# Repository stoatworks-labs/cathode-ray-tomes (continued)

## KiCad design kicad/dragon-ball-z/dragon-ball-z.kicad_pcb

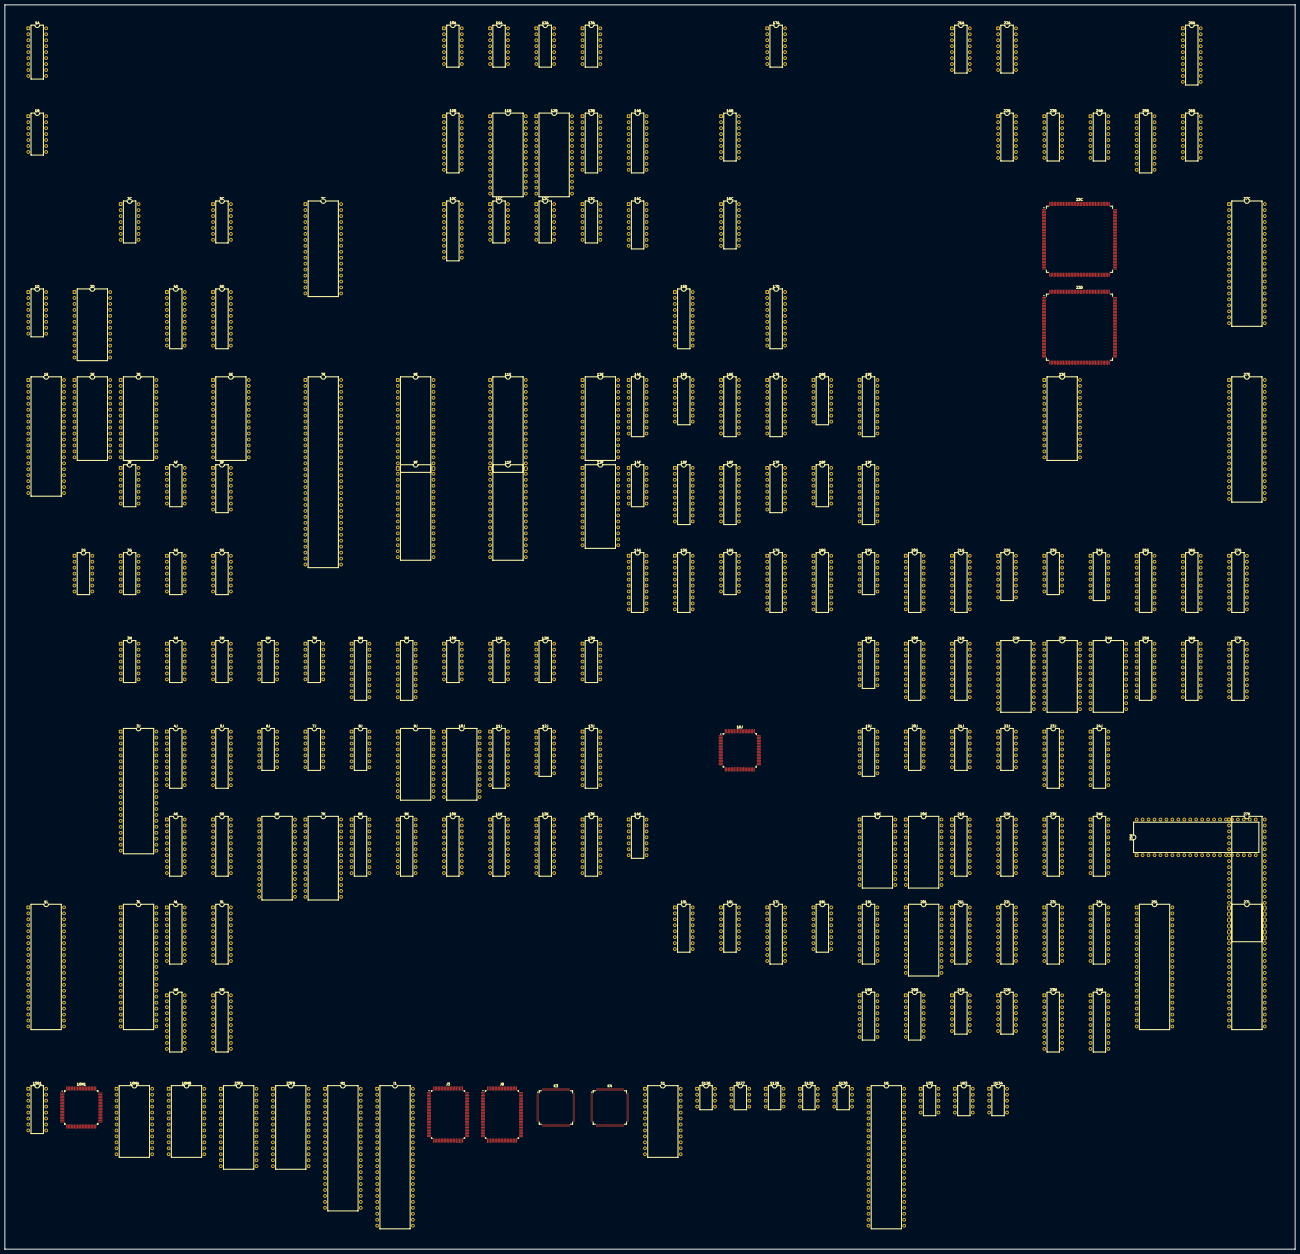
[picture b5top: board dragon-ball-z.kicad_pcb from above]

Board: 2 copper layers, 550.4 x 530.8 mm, 188 parts (0 on the bottom side), 1050 nets, no tracks yet.

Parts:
1A: DIP-18_W7.62mm
1B, 5C: DIP-14_W7.62mm
1D: YM3012; DIP-16_W7.62mm
1E: Z80; DIP-40_W15.24mm
1L, 3J, 3L, 25K, 25L, 27C, 27E, 27K, 27L: 065A08; DIP-42_W15.24mm
2D: YM2151; DIP-24_W15.24mm
2E, 3E, 23E, 23FA, 23FB: MB8464A-10W-15W; DIP-28_W15.24mm
2G: 74LS21; DIP-14_W7.62mm
3C: 4066; DIP-14_W7.62mm
3F, 4H, 5H, 7H, 7J, 11C, 14K, 17A: 74LS74; DIP-14_W7.62mm
3G, 3H, 13C, 14F, 16G, 18F, 22J: 74LS04; DIP-14_W7.62mm
4D, 8H, 9H: PAL16L8; DIP-20_W7.62mm
4F, 5G, 6J, 10H, 11H, 12C, 12H, 13H, 19G, 23G: 74LS32; DIP-14_W7.62mm
4G: 74LS10; DIP-14_W7.62mm
4J, 4K, 4L, 4M, 5D, 5J, 5K, 5L, 5M, 16F, 17E, 19E, 23L, 24J, 24K, 24L, 24M, 26H, 27H: 74LS374; DIP-20_W7.62mm
5E: 27256; DIP-28_W15.24mm
5F: 74LS148; DIP-16_W7.62mm
6H, 8J: 74LS08; DIP-14_W7.62mm
6K, 7K: MB8464A-80-10-15/L-LL; DIP-28_W15.24mm
7C: MS2M; DIP-32_W15.24mm
7E: 68000D; DIP-64_W15.24mm
8K, 9K, 10B, 10K, 11J, 11K, 12K, 13J, 13K, 14E, 14G, 25B, 26A: 74LS245; DIP-20_W7.62mm
9E, 9F, 11E, 11F: DIP-32_W15.24mm
9J, 10J, 16MA, 16MB: TMM2018_25_35_45; DIP-24_W15.24mm
10A, 11A, 12A, 13A: 74LS07; DIP-14_W7.62mm
10C, 13B, 14B, 15D, 17D, 17G, 17L: 74LS273; DIP-20_W7.62mm
11B, 12B, 13E, 13F: SRAM32K8B; DIP-28_W15.24mm
12J, 15L, 16L, 18L, 23B: 74LS367; DIP-16_W7.62mm
14C, 15B1, 16C, 17F, 18E, 19H, 19J, 19M, 20M, 22B, 22G, 24G: 74LS157; DIP-16_W7.62mm
15E, 16B: 74LS138; DIP-16_W7.62mm
15F, 19F, 20G, 20H, 21G, 21H, 21K, 22L, 23J, 23K, 23M, 27G: 74LS244; DIP-20_W7.62mm
15G, 19L, 21L, 22K, 25G, 25H: 74LS373; DIP-20_W7.62mm
16E: 74F245; DIP-20_W7.62mm
16H1, 16J: 053936; PQFP-80_14x14mm_P0.65mm
18G: PALACE16V8H-25; DIP-20_W7.62mm
19K, 20K, 20L, 22H, 23H, 24H: HM6116P-3; DIP-24_W15.24mm
20J, 21J, 21M, 22M: 74LS86; DIP-14_W7.62mm
21A, 22A, 24B, 26B: 74LS257; DIP-16_W7.62mm
23C: 054157; PQFP-160_28x28mm_P0.65mm
23D: 054156; PQFP-160_28x28mm_P0.65mm
26G: 74F374; DIP-20_W7.62mm
H1: 065A08; DIP-42_W15.24mm
I1: DIP-48_W15.24mm
J3, J8: 053251; PQFP-100_14x20mm_P0.65mm
K3: 053247; TQFP-120_14x14mm_P0.4mm
K4: 053246; TQFP-120_14x14mm_P0.4mm
S1: 051550; DIP-24_W15.24mm
S126, S127, S128, S129, S130: 005273; DIP-8_W7.62mm
U6: OKI6295; DIP-48_W15.24mm
U33, U63, U134: 052535; DIP-10_W7.62mm

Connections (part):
/3H10: 3F.11, 3H.10, 17G.11
/4D19: 4D.19, 11C.13
/4F6: 4F.6, 6H.13
/4HP5: 4H.5, 18G.7
/8H13: 8H.13, 9E.24, 9F.24, 11E.24, 11F.24, 18G.13
/8H19: 8H.19, 18G.5
/8JP11: 6H.4, 6J.4, 8J.11
/10C9: 10C.9, 14C.3
/10C12: 3F.4, 10C.12
/10h2: 3G.1, 3H.9, 3H.11, 3H.12, 7J.11, 10H.2, 19G.9, 19G.12, 23G.1
/12C2: 12C.2, 14C.12
/12C5: 12C.5, 14C.9
/13C8: 13C.3, 13C.8, 13C.11, 13C.13
/15E9: 15E.9, 18G.9, 23L.11, 26H.11
/16B11: 5D.11, 16B.11
/16B12: 10C.11, 16B.12
/16B14: 16B.14, 26A.19
/16B15: 18G.15, 23B.12, 25B.19
/16HCLK: 13C.4, 15D.11, 15G.11, 16F.11, 16H1.64, 17F.1, 19E.11, 19H.1, 22G.1, 24G.1, 24J.11, 25G.11, 25H.11, 26G.11, 27H.11
/16JCLK: 13C.10, 16J.64, 17D.11, 17E.11, 19J.1, 19L.11, 19M.1, 20M.1, 21L.11, 22K.11, 24K.11, 24L.11, 24M.11
/AS: 3H.2, 4H.4, 4H.10, 5H.4, 5H.10, 17G.1
/BCOL0: 17D.2, J3.4, J8.4, J8.51
/BCOL1: 17D.5, J3.5, J8.5, J8.52
/BCOL2: 17D.6, J3.6, J8.6, J8.54
/BCOL3: 17D.9, J3.7, J8.7, J8.55
/BCOL4: 17D.12, J3.55, J8.8
/BCOL5: 17D.15, J3.56, J8.9
/BDB0: 15F.18, 15G.3, 16F.3, 22H.9
/BDB1: 15F.16, 15G.4, 16F.4, 22H.10
/BDB2: 15F.14, 15G.7, 16F.7, 22H.11
/BDB3: 15F.12, 15G.8, 16F.8, 22H.13
/BDB4: 15F.9, 15G.13, 16F.13, 22H.14
/BDB5: 15F.7, 15G.14, 16F.14, 22H.15
/BDB6: 15F.5, 15G.17, 16F.17, 20J.2, 21J.2, 21J.5, 21J.13, 22H.16
/BDB7: 15F.3, 15G.18, 20J.5, 20J.10, 20J.13, 21J.9, 22H.17
/BDB8: 20H.18, 23H.9, 25H.3, 27H.3
/BDB9: 20H.16, 23H.10, 25H.4, 27H.4
/BDB10: 20H.14, 23H.11, 25H.7, 27H.7
/BDB11: 20H.12, 23H.13, 25H.8, 27H.8
/BDB12: 20H.9, 23H.14, 25H.13, 27H.13
/BDB13: 20H.7, 23H.15, 25H.14, 27H.14
/BDB14: 20H.5, 23H.16, 25H.17, 27H.17
/BDB15: 20H.3, 23H.17, 25H.18, 27H.18
/BDB16: 21H.18, 24H.9, 25G.3, 26G.3
/BDB17: 21H.16, 24H.10, 25G.4, 26G.4
/BDB18: 21H.14, 24H.11, 25G.7, 26G.7
/BDB19: 21H.12, 24H.13, 25G.8, 26G.8
/BDB20: 21H.9, 24H.14, 25G.13, 26G.13
/BDB21: 21H.7, 24H.15, 25G.14, 26G.14
/BDB22: 21H.5, 24H.16, 25G.17, 26G.17
/BDB23: 21H.3, 24H.17, 25G.18, 26G.18
/BNK~SCR: 15E.13, 23C.64
/CI0: 23C.154, J3.57, J8.57
/CI1: 23C.153, J3.58, J8.58
/CI2: 23C.51, J3.59, J8.59
/CI3: 23C.52, J3.60, J8.60
/CI4: 23C.143, J8.61
/CI5: 23C.142, J8.62
/CI6: 23C.141, J8.63
/CI7: 23C.138, J8.64
/CLK1: 3H.13, I1.8
/CLK2: 22J.5, I1.9
/CLKMIX: 3G.3, 7H.12, 11C.3, 13B.11, 13C.12, 14B.11, 14K.11, 17A.3, 17A.11, J3.41, J8.41
/COA7: 16C.3, J3.11
/COA8: 16C.6, J3.93
/COA9: 16C.10, J3.92
/COA10: 16C.13, J3.91
/COB0: 15B1.3, J8.19
/COB1: 15B1.6, J8.18
/COB2: 15B1.10, J8.17
/COB3: 15B1.13, J8.16
/COB4: 22B.3, J8.14
/COB5: 22B.6, J8.13
/COB6: 22B.10, J8.12
/COB7: 22B.13, J8.11
/COIN_CNT_1: S1.22, S1.23
/COIN_CNT_2: S1.20, S1.21
/CPG~CS: 16B.7, J3.81, J8.81
/CR~CS: 15E.15, K3.9
/CTRB: 3C.5, 5D.1, 10C.16, 14F.13
/DAO: 5C.3, U6.36
/FCOL0: 23C.152, J3.66, J8.66
/FCOL1: 23C.151, J3.67, J8.67
/FCOL2: 23C.53, J3.68, J8.68
/FCOL3: 23C.54, J3.69, J8.69
/FPAL0: 23C.135, J8.70
/FPAL1: 23C.134, J8.71
/FPAL2: 23C.133, J8.72
/FPAL3: 23C.132, J8.73
/GFXROMA0: 23D.159, 27C.10, 27E.10
/GFXROMA1: 23D.158, 27C.9, 27E.9
/GFXROMA2: 23D.157, 27C.8, 27E.8
/GFXROMA3: 23D.156, 27C.7, 27E.7
/GFXROMA4: 23D.155, 27C.6, 27E.6
/GFXROMA5: 23D.154, 27C.5, 27E.5
/GFXROMA6: 23D.153, 27C.4, 27E.4
/GFXROMA7: 23D.152, 27C.3, 27E.3
/GFXROMA8: 23D.151, 27C.41, 27E.41
/GFXROMA9: 23D.149, 27C.40, 27E.40
/GFXROMA10: 23D.148, 27C.39, 27E.39
/GFXROMA11: 23D.147, 27C.38, 27E.38
/GFXROMA12: 23D.146, 27C.37, 27E.37
/GFXROMA13: 23D.145, 27C.36, 27E.36
/GFXROMA14: 23D.144, 27C.35, 27E.35
/GFXROMA15: 23D.143, 27C.34, 27E.34
/GFXROMA16: 23D.142, 27C.33, 27E.33
/GFXROMA17: 23D.141, 27C.2, 27E.2
/GFXROMA18: 23D.138, 27C.1, 27E.1
/GFXROMD0: 23C.16, 27C.14
/GFXROMD1: 23C.17, 27C.16
/GFXROMD2: 23C.18, 27C.18
/GFXROMD3: 23C.19, 27C.20
/GFXROMD4: 23C.9, 27C.23
/GFXROMD5: 23C.11, 27C.25
/GFXROMD6: 23C.12, 27C.27
/GFXROMD7: 23C.13, 27C.29
/GFXROMD8: 23C.3, 27C.15
/GFXROMD9: 23C.4, 27C.17
/GFXROMD10: 23C.5, 27C.19
/GFXROMD11: 23C.6, 27C.21
/GFXROMD12: 23C.155, 27C.24
/GFXROMD13: 23C.156, 27C.26
/GFXROMD14: 23C.157, 27C.28
/GFXROMD15: 23C.158, 27C.30
/GFXROMD16: 23C.44, 27E.14
/GFXROMD17: 23C.45, 27E.16
/GFXROMD18: 23C.46, 27E.18
/GFXROMD19: 23C.47, 27E.20
/GFXROMD20: 23C.36, 27E.23
/GFXROMD21: 23C.37, 27E.25
/GFXROMD22: 23C.38, 27E.27
/GFXROMD23: 23C.39, 27E.29
/GFXROMD24: 23C.29, 27E.15
/GFXROMD25: 23C.31, 27E.17
/GFXROMD26: 23C.32, 27E.19
/GFXROMD27: 23C.33, 27E.21
/GFXROMD28: 23C.23, 27E.24
/GFXROMD29: 23C.24, 27E.26
/GFXROMD30: 23C.25, 27E.28
/GFXROMD31: 23C.26, 27E.30
/IO/1P_BTN_1_D: 22A.11, S126.3
/IO/1P_BTN_2_D: 22A.5, S128.7
/IO/1P_BTN_3_D: 22A.2, S128.3
/IO/1P_DOWN_D: 21A.14, S130.5
/IO/1P_LEFT_D: 24B.11, S130.3
/IO/1P_RIGHT_D: 24B.5, S126.7
/IO/1P_START_D: 22A.6, S127.7
/IO/1P_UP_D: 24B.2, S127.3
/IO/2P_BTN_1_D: 21A.11, S126.1
/IO/2P_BTN_2_D: 21A.5, S128.5
/IO/2P_BTN_3_D: 21A.2, S128.1
/IO/2P_DOWN_D: 22A.14, S130.7
/IO/2P_LEFT_D: 26B.11, S130.1
/IO/2P_RIGHT_D: 26B.5, S126.5
/IO/2P_START_D: 22A.3, S127.5
/IO/2P_UP_D: 26B.2, S127.1
/IO/COIN_1_D: 24B.6, S129.3
/IO/COIN_2_D: 24B.3, S129.1
/IO/SERVICE1_D: 22A.10, S129.7
/IO/TEST_D: 22A.13, S129.5
/IO/VSS: 21A.3, 21A.6, 23B.1, 23B.15, 24B.10, 24B.13, 24B.14, 26B.14
/IOE: 16B.15, 21A.15, 22A.15, 24B.15, 26B.15
/IPL0: 5F.9, 7E.25
/IPL1: 5F.7, 7E.24
/IPL2: 5F.6, 7E.23
/M16B: 3G.2, 14F.3, 23B.2, 23C.111, 23D.122
/MAIN_A1: 7E.29, 9E.12, 9F.12, 11E.12, 11F.12, 12J.2, 13E.10, 13F.10, 14G.2, 16L.2, J3.85, J8.85
/MAIN_A2: 7E.30, 9E.11, 9F.11, 11E.11, 11F.11, 12J.4, 13E.9, 13F.9, 14G.3, 16L.4, J3.84, J8.84
/MAIN_A3: 7E.31, 9E.10, 9F.10, 11E.10, 11F.10, 12J.6, 13E.8, 13F.8, 14G.4, 16L.6, J3.83, J8.83
/MAIN_A4: 7E.32, 9E.9, 9F.9, 11E.9, 11F.9, 12J.10, 13E.7, 13F.7, 14G.5, 16L.10, J3.82, J8.82
/MAIN_A5: 7E.33, 9E.8, 9F.8, 11E.8, 11F.8, 12J.12, 13E.6, 13F.6, 14G.6, 16L.12
/MAIN_A6: 7E.34, 9E.7, 9F.7, 11E.7, 11F.7, 12J.14, 13E.5, 13F.5, 14G.7, 16L.14
/MAIN_A7: 7E.35, 9E.6, 9F.6, 11E.6, 11F.6, 13E.4, 13F.4, 14G.8, 15L.2, 18L.2
/MAIN_A8: 7E.36, 9E.5, 9F.5, 11E.5, 11F.5, 13E.3, 13F.3, 14G.9, 15L.4, 18L.4
/MAIN_A9: 7E.37, 9E.27, 9F.27, 11E.27, 11F.27, 13E.25, 13F.25, 15L.6, 16E.2, 18L.6
/MAIN_A10: 7E.38, 9E.26, 9F.26, 11E.26, 11F.26, 13E.24, 13F.24, 15L.10, 16E.3, 18L.10
/MAIN_A11: 7E.39, 9E.23, 9F.23, 11E.23, 11F.23, 13E.21, 13F.21, 15L.12, 16E.4, 18L.12
/MAIN_A12: 7E.40, 9E.25, 9F.25, 11E.25, 11F.25, 13E.23, 13F.23, 15L.14, 16E.5, 18L.14
/MAIN_A13: 7E.41, 9E.4, 9F.4, 11E.4, 11F.4, 13E.2, 13F.2, 16E.6
/MAIN_A14: 7E.42, 9E.28, 9F.28, 11E.28, 11F.28, 13E.26, 13F.26, 16E.7
/MAIN_A15: 7E.43, 8H.11, 9E.29, 9F.29, 9H.11, 11E.29, 11F.29, 13E.1, 13F.1, 16E.8
/MAIN_A16: 7E.44, 8H.9, 9E.3, 9F.3, 9H.9, 11E.3, 11F.3, 16E.9
/MAIN_A17: 7E.45, 8H.8, 9E.2, 9F.2, 9H.8, 11E.2, 11F.2, 13C.5, 16B.6
/MAIN_A18: 7E.46, 8H.7, 9E.30, 9F.30, 9H.7, 11E.30, 11F.30
/MAIN_A19: 7E.47, 8H.6, 9E.31, 9F.31, 9H.6, 11E.31, 11F.31
/MAIN_A20: 7E.48, 8H.5, 9H.5
/MAIN_A21: 7E.50, 8H.4, 9H.4
/MAIN_A22: 7E.51, 8H.3, 9H.3
/MAIN_A23: 7E.52, 8H.2, 9H.2
/MAIN_AB0: 3H.3, 5G.1, 11K.2, 12H.1, 14G.18, 15B1.2, 16H1.74, 16J.74, 23B.10, 23C.74, 23D.95, 23J.2, 23M.2, 24G.6, I1.42, K3.7, K4.7
/MAIN_AB1: 11K.3, 14G.17, 15B1.5, 16H1.72, 16J.72, 21A.1, 22A.1, 23B.6, 23C.75, 23D.96, 23J.4, 24B.1, 26B.1, I1.41, K3.6, K4.6
/MAIN_AB2: 11K.4, 14G.16, 15B1.11, 16H1.71, 16J.71, 23D.97, 23J.6, 23M.4, I1.40
/MAIN_AB3: 11K.5, 14G.15, 15B1.14, 16H1.70, 16J.70, 23D.98, 23J.8, 23M.6, I1.38
/MAIN_AB4: 11K.6, 14G.14, 22B.2, 23D.99, 23J.11, 23M.8
/MAIN_AB5: 11K.7, 14G.13, 22B.5, 23D.101, 23J.13, 23M.11
/MAIN_AB6: 11K.8, 14G.12, 22B.11, 23D.102, 23J.15, 23M.13
/MAIN_AB7: 11K.9, 14G.11, 22B.14, 23D.103, 23J.17, 23M.15
/MAIN_AB8: 8K.2, 16C.2, 16E.18, 23D.104, 23K.2, 23M.17, 27G.2
/MAIN_AB9: 8K.3, 16C.5, 16E.17, 23D.105, 23K.4, 27G.4
/MAIN_AB10: 8K.4, 16C.11, 16E.16, 23D.106, 23K.6, 27G.6
/MAIN_AB11: 8K.5, 16C.14, 16E.15, 23D.107, 23K.8, 27G.8
/MAIN_AB12: 8K.6, 16E.14, 18G.19, 23D.108, 23K.11, 27G.11
/MAIN_AB13: 14C.2, 15E.1, 16B.1, 16E.13, 23K.13, 27G.13
/MAIN_AB14: 15E.2, 16B.2, 16E.12, 23K.15, 27G.15
/MAIN_AB15: 15E.3, 16B.3, 16E.11, 23K.17, 27G.17
/MAIN_D0: 5D.3, 7E.5, 9F.13, 9K.2, 10B.2, 10C.3, 13F.11, 18G.12, 22A.4, 23C.76, 23D.76, 25B.2, 26A.18, I1.13, J3.80, J8.80, K3.30
/MAIN_D1: 5D.4, 7E.4, 9F.14, 9K.3, 10B.3, 10C.4, 13F.12, 22A.7, 23C.77, 23D.77, 25B.3, 26A.17, I1.14, J3.79, J8.79, K3.29
/MAIN_D2: 5D.7, 7E.3, 9F.15, 9K.4, 10B.4, 10C.7, 13F.13, 22A.12, 23C.78, 23D.78, 25B.4, 26A.16, I1.15, J3.77, J8.77, K3.28
/MAIN_D3: 5D.8, 7E.2, 9F.17, 9K.5, 10B.5, 10C.8, 13F.15, 22A.9, 23C.79, 23D.79, 25B.5, 26A.15, I1.16, J3.76, J8.76, K3.27
/MAIN_D4: 5D.13, 7E.1, 9F.18, 9K.6, 10B.6, 10C.13, 13F.16, 23C.82, 23D.82, 24B.4, 25B.6, 26A.14, I1.18, J3.75, J8.75, K3.26
/MAIN_D5: 5D.14, 7E.64, 9F.19, 9K.7, 10B.7, 10C.14, 13F.17, 23C.83, 23D.83, 24B.7, 25B.7, 26A.13, I1.19, J3.74, J8.74, K3.25
/MAIN_D6: 5D.17, 7E.63, 9F.20, 9K.8, 10B.8, 10C.17, 13F.18, 23C.84, 23D.84, 24B.12, 25B.8, 26A.12, I1.20, K3.24
/MAIN_D7: 5D.18, 7E.62, 9F.21, 9K.9, 10B.9, 10C.18, 13F.19, 23C.85, 23D.85, 24B.9, 25B.9, 26A.11, I1.21, K3.23
/MAIN_D8: 7E.61, 9E.13, 10K.2, 13E.11, 14E.2, 21A.4, 23C.86, 23D.86, K3.22
/MAIN_D9: 7E.60, 9E.14, 10K.3, 13E.12, 14E.3, 21A.7, 23C.87, 23D.87, K3.20
/MAIN_D10: 7E.59, 9E.15, 10K.4, 13E.13, 14E.4, 21A.9, 23C.88, 23D.88, K3.19
/MAIN_D11: 7E.58, 9E.17, 10K.5, 13E.15, 14E.5, 21A.12, 23C.89, 23D.89, K3.18
/MAIN_D12: 7E.57, 9E.18, 10K.6, 13E.16, 14E.6, 23C.91, 23D.91, 26B.4, K3.17
/MAIN_D13: 7E.56, 9E.19, 10K.7, 13E.17, 14E.7, 23C.92, 23D.92, 26B.7, K3.15
/MAIN_D14: 7E.55, 9E.20, 10K.8, 13E.18, 14E.8, 23C.93, 23D.93, 26B.12, K3.14
/MAIN_D15: 7E.54, 9E.21, 10K.9, 13E.19, 14E.9, 23C.94, 23D.94, 26B.9, K3.13
/MAIN_PSAC/MAIN_D0: 11J.2, 12K.2, 15F.2, 19F.18, 20G.18, 21G.2
/MAIN_PSAC/MAIN_D1: 11J.3, 12K.3, 15F.4, 19F.16, 20G.16, 21G.4
/MAIN_PSAC/MAIN_D2: 11J.4, 12K.4, 15F.6, 19F.14, 20G.14, 21G.6
/MAIN_PSAC/MAIN_D3: 11J.5, 12K.5, 15F.8, 19F.12, 20G.12, 21G.8
/MAIN_PSAC/MAIN_D4: 11J.6, 12K.6, 15F.11, 19F.9, 20G.9, 21G.11
/MAIN_PSAC/MAIN_D5: 11J.7, 12K.7, 15F.13, 19F.7, 20G.7, 21G.13
/MAIN_PSAC/MAIN_D6: 11J.8, 12K.8, 15F.15, 19F.5, 20G.5, 21G.15
/MAIN_PSAC/MAIN_D7: 11J.9, 12K.9, 15F.17, 19F.3, 20G.3, 21G.17
/MAIN_PSAC/MAIN_D8: 13J.2, 13K.2
/MAIN_PSAC/MAIN_D9: 13J.3, 13K.3
/MAIN_PSAC/MAIN_D10: 13J.4, 13K.4
/MAIN_PSAC/MAIN_D11: 13J.5, 13K.5
/MAIN_PSAC/MAIN_D12: 13J.6, 13K.6
/MAIN_PSAC/MAIN_D13: 13J.7, 13K.7
/MAIN_PSAC/MAIN_D14: 13J.8, 13K.8
/MAIN_PSAC/MAIN_D15: 13J.9, 13K.9
/MAIN_PSAC/MOROE0: 8J.13, 9H.19, 12H.4
/MAIN_PSAC/MOROE4: 5G.4, 9H.15, 23G.4, 23G.12
/MAIN_PSAC/MOROE7: 6H.1, 6J.1, 9H.12
/MAIN_PSAC/NDMA_A: 16G.5, 16J.47
/MAIN_PSAC/NDMA_B: 16G.9, 16H1.47
/MAIN_PSAC/POEB: 4F.3, 15F.1, 15F.19, 20H.1, 20H.19, 21H.1, 21H.19
/MAIN_PSAC/PSAC_1/LA0: 16J.53, 16L.7, 16MA.6, 16MB.6
/MAIN_PSAC/PSAC_1/LA1: 16J.54, 16L.9, 16MA.5, 16MB.5
/MAIN_PSAC/PSAC_1/LA2: 16J.55, 16L.11, 16MA.4, 16MB.4
/MAIN_PSAC/PSAC_1/LA3: 16J.56, 16L.13, 16MA.3, 16MB.3
/MAIN_PSAC/PSAC_1/LA4: 15L.3, 16J.57, 16MA.2, 16MB.2
/MAIN_PSAC/PSAC_1/LA5: 15L.5, 16J.58, 16MA.1, 16MB.1
/MAIN_PSAC/PSAC_1/LA6: 15L.7, 16J.59, 16MA.23, 16MB.23
/MAIN_PSAC/PSAC_1/LA7: 15L.9, 16J.60, 16MA.22, 16MB.22
/MAIN_PSAC/PSAC_1/LA8: 15L.11, 16J.61, 16MA.19, 16MB.19
/MAIN_PSAC/PSAC_1/LH1: 16J.50, 16L.3, 16MA.8, 16MB.8
/MAIN_PSAC/PSAC_1/LH2: 16J.51, 16L.5, 16MA.7, 16MB.7
/MAIN_PSAC/PSAC_1/LUTD0: 12K.18, 16J.29, 16MB.9
/MAIN_PSAC/PSAC_1/LUTD1: 12K.17, 16J.30, 16MB.10
/MAIN_PSAC/PSAC_1/LUTD2: 12K.16, 16J.31, 16MB.11
/MAIN_PSAC/PSAC_1/LUTD3: 12K.15, 16J.32, 16MB.13
/MAIN_PSAC/PSAC_1/LUTD4: 12K.14, 16J.34, 16MB.14
/MAIN_PSAC/PSAC_1/LUTD5: 12K.13, 16J.35, 16MB.15
/MAIN_PSAC/PSAC_1/LUTD6: 12K.12, 16J.36, 16MB.16
/MAIN_PSAC/PSAC_1/LUTD7: 12K.11, 16J.37, 16MB.17
/MAIN_PSAC/PSAC_1/LUTD8: 13K.18, 16J.38, 16MA.9
/MAIN_PSAC/PSAC_1/LUTD9: 13K.17, 16J.39, 16MA.10
/MAIN_PSAC/PSAC_1/LUTD10: 13K.16, 16J.40, 16MA.11
/MAIN_PSAC/PSAC_1/LUTD11: 13K.15, 16J.41, 16MA.13
/MAIN_PSAC/PSAC_1/LUTD12: 13K.14, 16J.43, 16MA.14
/MAIN_PSAC/PSAC_1/LUTD13: 13K.13, 16J.44, 16MA.15
/MAIN_PSAC/PSAC_1/LUTD14: 13K.12, 16J.45, 16MA.16
/MAIN_PSAC/PSAC_1/LUTD15: 13K.11, 16J.46, 16MA.17
/MAIN_PSAC/PSAC_1/ROM1/BD0: 19K.9, 19L.3, 22L.18, 24L.3
/MAIN_PSAC/PSAC_1/ROM1/BD1: 19K.10, 19L.4, 22L.16, 24L.4
/MAIN_PSAC/PSAC_1/ROM1/BD2: 19K.11, 19L.7, 22L.14, 24L.7
/MAIN_PSAC/PSAC_1/ROM1/BD3: 19K.13, 19L.8, 22L.12, 24L.8
/MAIN_PSAC/PSAC_1/ROM1/BD4: 19K.14, 19L.13, 22L.9, 24L.13
/MAIN_PSAC/PSAC_1/ROM1/BD5: 19K.15, 19L.14, 22L.7, 24L.14
/MAIN_PSAC/PSAC_1/ROM1/BD6: 19K.16, 19L.17, 21M.5, 21M.10, 22L.5, 22M.5, 22M.10, 24L.17
/MAIN_PSAC/PSAC_1/ROM1/BD7: 19K.17, 19L.18, 21M.2, 21M.13, 22L.3, 22M.2, 22M.13, 24L.18
/MAIN_PSAC/PSAC_1/ROM1/BD8: 20K.9, 21K.18, 22K.3, 24K.3
/MAIN_PSAC/PSAC_1/ROM1/BD9: 20K.10, 21K.16, 22K.4, 24K.4
/MAIN_PSAC/PSAC_1/ROM1/BD10: 20K.11, 21K.14, 22K.7, 24K.7
/MAIN_PSAC/PSAC_1/ROM1/BD11: 20K.13, 21K.12, 22K.8, 24K.8
/MAIN_PSAC/PSAC_1/ROM1/BD12: 20K.14, 21K.9, 22K.13, 24K.13
/MAIN_PSAC/PSAC_1/ROM1/BD13: 20K.15, 21K.7, 22K.14, 24K.14
/MAIN_PSAC/PSAC_1/ROM1/BD14: 20K.16, 21K.5, 22K.17, 24K.17
/MAIN_PSAC/PSAC_1/ROM1/BD15: 20K.17, 21K.3, 22K.18, 24K.18
/MAIN_PSAC/PSAC_1/ROM1/BD16: 20L.9, 21L.3
/MAIN_PSAC/PSAC_1/ROM1/BD17: 20L.10, 21L.4
/MAIN_PSAC/PSAC_1/ROM1/BD18: 20L.11, 21L.7
/MAIN_PSAC/PSAC_1/ROM1/BD19: 20L.13, 21L.8
/MAIN_PSAC/PSAC_1/ROM1/BD20: 20L.14, 21L.13
/MAIN_PSAC/PSAC_1/ROM1/BD21: 20L.15, 21L.14
/MAIN_PSAC/PSAC_1/ROM1/BD22: 20L.16, 21L.17
/MAIN_PSAC/PSAC_1/ROM1/BD23: 20L.17, 21L.18
/MAIN_PSAC/PSAC_1/ROM1/DK1: 23L.19, 24K.19
/MAIN_PSAC/PSAC_1/ROM1/MAIN_D0: 19L.2, 21L.2, 22L.2, 23L.3
/MAIN_PSAC/PSAC_1/ROM1/MAIN_D1: 19L.5, 21L.5, 22L.4, 23L.4
/MAIN_PSAC/PSAC_1/ROM1/MAIN_D2: 19L.6, 21L.6, 22L.6, 23L.7
/MAIN_PSAC/PSAC_1/ROM1/MAIN_D3: 19L.9, 21L.9, 22L.8, 23L.8
/MAIN_PSAC/PSAC_1/ROM1/MAIN_D4: 19L.12, 21L.12, 22L.11, 23L.13
/MAIN_PSAC/PSAC_1/ROM1/MAIN_D5: 19L.15, 21L.15, 22L.13, 23L.14
/MAIN_PSAC/PSAC_1/ROM1/MAIN_D6: 19L.16, 21L.16, 22L.15, 23L.17
/MAIN_PSAC/PSAC_1/ROM1/MAIN_D7: 19L.19, 21L.19, 22L.17, 23L.18
/MAIN_PSAC/PSAC_1/ROM1/MAIN_D8: 21K.2, 22K.2
/MAIN_PSAC/PSAC_1/ROM1/MAIN_D9: 21K.4, 22K.5
/MAIN_PSAC/PSAC_1/ROM1/MAIN_D10: 21K.6, 22K.6
/MAIN_PSAC/PSAC_1/ROM1/MAIN_D11: 21K.8, 22K.9
/MAIN_PSAC/PSAC_1/ROM1/MAIN_D12: 21K.11, 22K.12
/MAIN_PSAC/PSAC_1/ROM1/MAIN_D13: 21K.13, 22K.15
/MAIN_PSAC/PSAC_1/ROM1/MAIN_D14: 21K.15, 22K.16
/MAIN_PSAC/PSAC_1/ROM1/MAIN_D15: 21K.17, 22K.19
/MAIN_PSAC/PSAC_1/ROM1/PLOE: 23L.16, 24K.16, 25L.13
/MAIN_PSAC/PSAC_1/ROM1/RA_LOW: 23M.16, 24M.5, 25L.30
/MAIN_PSAC/PSAC_1/ROM1/VA0: 19K.8, 20K.8, 20L.8, 20M.7
/MAIN_PSAC/PSAC_1/ROM1/VA1: 19K.7, 20K.7, 20L.7, 20M.9
/MAIN_PSAC/PSAC_1/ROM1/VA2: 19K.6, 20K.6, 20L.6, 20M.12
/MAIN_PSAC/PSAC_1/ROM1/VA3: 19K.5, 19M.4, 20K.5, 20L.5
/MAIN_PSAC/PSAC_1/ROM1/VA4: 19K.4, 19M.7, 20K.4, 20L.4
/MAIN_PSAC/PSAC_1/ROM1/VA5: 19K.3, 19M.9, 20K.3, 20L.3
/MAIN_PSAC/PSAC_1/ROM1/VA6: 19K.2, 19M.12, 20K.2, 20L.2
/MAIN_PSAC/PSAC_1/ROM1/VA7: 19J.4, 19K.1, 20K.1, 20L.1
/MAIN_PSAC/PSAC_1/ROM1/VA8: 19J.7, 19K.23, 20K.23, 20L.23
/MAIN_PSAC/PSAC_1/ROM1/VA9: 19J.9, 19K.22, 20K.22, 20L.22
/MAIN_PSAC/PSAC_1/ROM1/VA10: 19J.12, 19K.19, 20K.19, 20L.19
/MAIN_PSAC/PSAC_1/VSS: 16J.2, 16J.12, 16J.23, 16J.28, 16J.42, 16J.52, 16J.63, 16J.75, 16MA.18, 16MB.18
/MAIN_PSAC/PSAC_1/X0: 16J.26, 21M.1
/MAIN_PSAC/PSAC_1/X1: 16J.25, 22M.1
/MAIN_PSAC/PSAC_1/X2: 16J.24, 21M.12
/MAIN_PSAC/PSAC_1/X3: 16J.22, 22M.12
/MAIN_PSAC/PSAC_1/X4: 16J.21, 20M.5
/MAIN_PSAC/PSAC_1/X5: 16J.20, 20M.11
/MAIN_PSAC/PSAC_1/X6: 16J.19, 20M.14
/MAIN_PSAC/PSAC_1/X7: 16J.18, 19M.2
/MAIN_PSAC/PSAC_1/X8: 16J.17, 19M.5
/MAIN_PSAC/PSAC_1/X9: 16J.16, 19M.11
/MAIN_PSAC/PSAC_1/Y0: 16J.10, 22M.4
/MAIN_PSAC/PSAC_1/Y1: 16J.9, 21M.9
/MAIN_PSAC/PSAC_1/Y2: 16J.8, 21M.4
/MAIN_PSAC/PSAC_1/Y3: 16J.7, 22M.9
/MAIN_PSAC/PSAC_1/Y4: 16J.6, 19M.14
/MAIN_PSAC/PSAC_1/Y5: 16J.5, 19J.2
/MAIN_PSAC/PSAC_1/Y6: 16J.4, 19J.5
/MAIN_PSAC/PSAC_1/Y7: 16J.3, 19J.11
/MAIN_PSAC/PSAC_1/Y8: 16J.1, 19J.14
/MAIN_PSAC/PSAC_2/6JP3: 6J.3, 6J.10, 11H.5
/MAIN_PSAC/PSAC_2/LA0: 9J.6, 10J.6, 12J.7, 16H1.53
/MAIN_PSAC/PSAC_2/LA1: 9J.5, 10J.5, 12J.9, 16H1.54
/MAIN_PSAC/PSAC_2/LA2: 9J.4, 10J.4, 12J.11, 16H1.55
/MAIN_PSAC/PSAC_2/LA3: 9J.3, 10J.3, 12J.13, 16H1.56
/MAIN_PSAC/PSAC_2/LA4: 9J.2, 10J.2, 16H1.57, 18L.3
/MAIN_PSAC/PSAC_2/LA5: 9J.1, 10J.1, 16H1.58, 18L.5
/MAIN_PSAC/PSAC_2/LA6: 9J.23, 10J.23, 16H1.59, 18L.7
/MAIN_PSAC/PSAC_2/LA7: 9J.22, 10J.22, 16H1.60, 18L.9
/MAIN_PSAC/PSAC_2/LA8: 9J.19, 10J.19, 16H1.61, 18L.11
/MAIN_PSAC/PSAC_2/LH1: 9J.8, 10J.8, 12J.3, 16H1.50
/MAIN_PSAC/PSAC_2/LH2: 9J.7, 10J.7, 12J.5, 16H1.51
/MAIN_PSAC/PSAC_2/LUTD0: 9J.9, 11J.18, 16H1.29
/MAIN_PSAC/PSAC_2/LUTD1: 9J.10, 11J.17, 16H1.30
/MAIN_PSAC/PSAC_2/LUTD2: 9J.11, 11J.16, 16H1.31
/MAIN_PSAC/PSAC_2/LUTD3: 9J.13, 11J.15, 16H1.32
/MAIN_PSAC/PSAC_2/LUTD4: 9J.14, 11J.14, 16H1.34
/MAIN_PSAC/PSAC_2/LUTD5: 9J.15, 11J.13, 16H1.35
/MAIN_PSAC/PSAC_2/LUTD6: 9J.16, 11J.12, 16H1.36
/MAIN_PSAC/PSAC_2/LUTD7: 9J.17, 11J.11, 16H1.37
/MAIN_PSAC/PSAC_2/LUTD8: 10J.9, 13J.18, 16H1.38
/MAIN_PSAC/PSAC_2/LUTD9: 10J.10, 13J.17, 16H1.39
/MAIN_PSAC/PSAC_2/LUTD10: 10J.11, 13J.16, 16H1.40
/MAIN_PSAC/PSAC_2/LUTD11: 10J.13, 13J.15, 16H1.41
/MAIN_PSAC/PSAC_2/LUTD12: 10J.14, 13J.14, 16H1.43
/MAIN_PSAC/PSAC_2/LUTD13: 10J.15, 13J.13, 16H1.44
/MAIN_PSAC/PSAC_2/LUTD14: 10J.16, 13J.12, 16H1.45
/MAIN_PSAC/PSAC_2/LUTD15: 10J.17, 13J.11, 16H1.46
/MAIN_PSAC/PSAC_2/ROM2/DK2: 26G.19, 26H.19
/MAIN_PSAC/PSAC_2/ROM2/MAIN_D0: 15G.2, 20H.2, 25H.2, 26H.3
/MAIN_PSAC/PSAC_2/ROM2/MAIN_D1: 15G.5, 20H.4, 25H.5, 26H.4
/MAIN_PSAC/PSAC_2/ROM2/MAIN_D2: 15G.6, 20H.6, 25H.6, 26H.7
/MAIN_PSAC/PSAC_2/ROM2/MAIN_D3: 15G.9, 20H.8, 25H.9, 26H.8
/MAIN_PSAC/PSAC_2/ROM2/MAIN_D4: 15G.12, 20H.11, 25H.12, 26H.13
/MAIN_PSAC/PSAC_2/ROM2/MAIN_D5: 15G.15, 20H.13, 25H.15, 26H.14
/MAIN_PSAC/PSAC_2/ROM2/MAIN_D6: 15G.16, 20H.15, 25H.16, 26H.17
/MAIN_PSAC/PSAC_2/ROM2/MAIN_D7: 15G.19, 20H.17, 25H.19, 26H.18
/MAIN_PSAC/PSAC_2/ROM2/MAIN_D8: 21H.2, 25G.2
/MAIN_PSAC/PSAC_2/ROM2/MAIN_D9: 21H.4, 25G.5
/MAIN_PSAC/PSAC_2/ROM2/MAIN_D10: 21H.6, 25G.6
/MAIN_PSAC/PSAC_2/ROM2/MAIN_D11: 21H.8, 25G.9
/MAIN_PSAC/PSAC_2/ROM2/MAIN_D12: 21H.11, 25G.12
/MAIN_PSAC/PSAC_2/ROM2/MAIN_D13: 21H.13, 25G.15
/MAIN_PSAC/PSAC_2/ROM2/MAIN_D14: 21H.15, 25G.16
/MAIN_PSAC/PSAC_2/ROM2/MAIN_D15: 21H.17, 25G.19
/MAIN_PSAC/PSAC_2/ROM2/PKOE: 25K.13, 26G.16, 26H.16
/MAIN_PSAC/PSAC_2/ROM2/RB_LOW: 23J.16, 24J.5, 25K.30
/MAIN_PSAC/PSAC_2/ROM2/VAB0: 19H.7, 22H.8, 23H.8, 24H.8
/MAIN_PSAC/PSAC_2/ROM2/VAB1: 19H.9, 22H.7, 23H.7, 24H.7
/MAIN_PSAC/PSAC_2/ROM2/VAB2: 19H.12, 22H.6, 23H.6, 24H.6
/MAIN_PSAC/PSAC_2/ROM2/VAB3: 22G.4, 22H.5, 23H.5, 24H.5
/MAIN_PSAC/PSAC_2/ROM2/VAB4: 22G.7, 22H.4, 23H.4, 24H.4
/MAIN_PSAC/PSAC_2/ROM2/VAB5: 22G.9, 22H.3, 23H.3, 24H.3
/MAIN_PSAC/PSAC_2/ROM2/VAB6: 22G.12, 22H.2, 23H.2, 24H.2
/MAIN_PSAC/PSAC_2/ROM2/VAB7: 17F.4, 22H.1, 23H.1, 24H.1
/MAIN_PSAC/PSAC_2/ROM2/VAB8: 17F.7, 22H.23, 23H.23, 24H.23
/MAIN_PSAC/PSAC_2/ROM2/VAB9: 17F.9, 22H.22, 23H.22, 24H.22
/MAIN_PSAC/PSAC_2/ROM2/VAB10: 17F.12, 22H.19, 23H.19, 24H.19
/MAIN_PSAC/PSAC_2/VSS: 9J.18, 10J.18, 16H1.2, 16H1.12, 16H1.23, 16H1.28, 16H1.42, 16H1.52, 16H1.63, 16H1.75
/MAIN_PSAC/PSAC_2/X0: 16H1.26, 21J.10
/MAIN_PSAC/PSAC_2/X1: 16H1.25, 20J.12
/MAIN_PSAC/PSAC_2/X2: 16H1.24, 20J.4
/MAIN_PSAC/PSAC_2/X3: 16H1.22, 20J.9
/MAIN_PSAC/PSAC_2/X4: 16H1.21, 19H.5
/MAIN_PSAC/PSAC_2/X5: 16H1.20, 19H.11
/MAIN_PSAC/PSAC_2/X6: 16H1.19, 19H.14
/MAIN_PSAC/PSAC_2/X7: 16H1.18, 22G.2
/MAIN_PSAC/PSAC_2/X8: 16H1.17, 22G.5
/MAIN_PSAC/PSAC_2/X9: 16H1.16, 22G.11
/MAIN_PSAC/PSAC_2/Y0: 16H1.10, 21J.12
/MAIN_PSAC/PSAC_2/Y1: 16H1.9, 21J.4
/MAIN_PSAC/PSAC_2/Y2: 16H1.8, 20J.1
/MAIN_PSAC/PSAC_2/Y3: 16H1.7, 21J.1
/MAIN_PSAC/PSAC_2/Y4: 16H1.6, 22G.14
/MAIN_PSAC/PSAC_2/Y5: 16H1.5, 17F.2
/MAIN_PSAC/PSAC_2/Y6: 16H1.4, 17F.5
/MAIN_PSAC/PSAC_2/Y7: 16H1.3, 17F.11
/MAIN_PSAC/PSAC_2/Y8: 16H1.1, 17F.14
/MAIN_PSAC/PSAC_SEL: 4F.5, 4F.10, 6J.5, 12H.5, 12J.1, 12J.15, 14K.9, 15L.1, 15L.15, 16L.1, 16L.15, 18L.1, 18L.15
/MAIN_PSAC/PSCS1: 20K.18, 20L.18, 23H.18, 24G.4, 24H.18
/MAIN_PSAC/PSCS2: 19K.18, 22H.18, 24G.7
/MAIN_PSAC/PSCS3: 10H.4, 23G.13, 24G.9
/MAIN_PSAC/PSCS4: 23G.5, 23G.9, 24G.12
/MAIN_PSAC/VSS: 4G.3, 4G.4, 4G.5, 8H.10, 9H.10, 14C.6, 14C.15, 15B1.15, 16C.15, 17E.17, 22B.15, 24G.2, 24G.5, 24G.15
/MAIN_PSAC/WR_L: 10H.11, 11H.4, 13H.1, 13H.4, 14C.11, 24G.10
/MAIN_PSAC/~CEB: 4F.8, 11J.19, 13J.19
/MAIN_PSAC/~CEA: 6J.6, 12K.19, 13K.19
/MAIN_PSAC/~MAIN_AB0: 3H.4, 5G.10, 12H.9, 24G.3
/MAIN_PSAC/~PSAC_SEL: 6J.2, 8J.1, 8J.5, 14K.8, 16H1.48, 16H1.62, 16J.48, 16J.62
/MOROE1: 9H.18, 18F.5, 18F.11, 20G.1, 20G.19, 23K.1, 23K.19, 23L.1, 23M.1, 23M.19
/MOROE2: 9H.17, 18F.1, 18F.3, 19F.1, 19F.19, 23J.1, 23J.19, 26G.1, 26H.1, 27G.1, 27G.19
/MOROE3: 4H.2, 9H.16, 10H.5, 11H.2, 23G.10
/MOROE5: 9H.14, 14F.5
/MOROE6: 5H.2, 9H.13, 23D.112
/MPLXH: 8H.18, 15E.5, 16B.5
/MUSEL: 8H.17, 10B.19, 14C.1, 14E.19, 15B1.1, 16C.1, 22B.1
/M~RD: 3G.10, 5G.5, 8J.2, 8J.4, 8K.7, 9K.1, 10B.1, 10K.1, 11H.1, 11J.1, 12H.13, 12K.1, 13J.1, 13K.1, 14C.5, 14E.1
/NAMP: 5H.11, 23D.125
/NOBA: 16J.76, 17E.18
/NOBB: 16F.18, 16H1.76
/OBJCLK6: 22J.4, K3.12, K4.12
/OBJDMA: 8K.19, 11H.13, 11K.19, 14F.9, K4.116
/OBJ~REG: 15E.14, K3.2, K4.2
/OCHARA: 14F.10, K4.9
/OPAL8: 17L.3, K3.40
/OPRI0: 17L.4, K3.42
/OPRI1: 17L.7, K3.43
/OPRI2: 17L.8, K3.44
/OPRI3: 17L.13, K3.45
/OPRI4: 17L.14, K3.47
/PAL8HP16: 6H.5, 6J.13, 8H.16, 12C.9
/POEA: 5G.11, 21G.1, 21G.19, 21K.1, 21K.19, 22L.1, 22L.19
/PSDA0: 25L.14, 27L.14
/PSDA1: 25L.16, 27L.16
/PSDA2: 25L.18, 27L.18
/PSDA3: 25L.20, 27L.20
/PSDA4: 25L.23, 27L.23
/PSDA5: 25L.25, 27L.25
/PSDA6: 25L.27, 27L.27
/PSDA7: 25L.29, 27L.29
/PSDB0: 19E.3, 19F.2, 20G.2, 25K.14, 27K.14
/PSDB1: 19E.4, 19F.4, 20G.4, 25K.16, 27K.16
/PSDB2: 19E.7, 19F.6, 20G.6, 25K.18, 27K.18
/PSDB3: 19E.8, 19F.8, 20G.8, 25K.20, 27K.20
/PSDB4: 19E.13, 19F.11, 20G.11, 25K.23, 27K.23
/PSDB5: 19E.14, 19F.13, 20G.13, 25K.25, 27K.25
/PSDB6: 19E.17, 19F.15, 20G.15, 25K.27, 27K.27
/PSDB7: 19E.18, 19F.17, 20G.17, 25K.29, 27K.29
/PS~OE: 12H.11, 13E.22, 13F.22
/PS~WR1: 13E.27, 13H.11
/PS~WR2: 13F.27, 13H.3
/RA0: 23M.14, 24M.6, 25L.10, 27L.10
/RA1: 23M.12, 24M.9, 25L.9, 27L.9
/RA2: 23M.9, 24M.12, 25L.8, 27L.8
/RA3: 23M.7, 24M.15, 25L.7, 27L.7
/RA4: 23M.5, 24M.16, 25L.6, 27L.6
/RA5: 23M.3, 24M.19, 25L.5, 27L.5
/RA6: 23K.18, 24L.2, 25L.4, 27L.4
/RA7: 23K.16, 24L.5, 25L.3, 27L.3
/RA8: 23K.14, 24L.6, 25L.41, 27L.41
/RA9: 23K.12, 24L.9, 25L.40, 27L.40
/RA10: 23K.9, 24L.12, 25L.39, 27L.39
/RA11: 23K.7, 24L.15, 25L.38, 27L.38
/RA12: 23K.5, 24L.16, 25L.37, 27L.37
/RA13: 23K.3, 24L.19, 25L.36, 27L.36
/RA14: 23L.2, 24K.2, 25L.35, 27L.35
/RA15: 23L.5, 24K.5, 25L.34, 27L.34
/RA16: 23L.6, 24K.6, 25L.33, 27L.33
/RA17: 23L.9, 24K.9, 25L.2, 27L.2
/RA18: 23L.12, 24K.12, 25L.1, 27L.1
/RA19: 23L.15, 24K.15, 25L.42, 27L.42
/RB0: 23J.14, 24J.6, 25K.10, 27K.10
/RB1: 23J.12, 24J.9, 25K.9, 27K.9
/RB2: 23J.9, 24J.12, 25K.8, 27K.8
/RB3: 23J.7, 24J.15, 25K.7, 27K.7
/RB4: 23J.5, 24J.16, 25K.6, 27K.6
/RB5: 23J.3, 24J.19, 25K.5, 27K.5
/RB6: 25K.4, 27G.18, 27H.2, 27K.4
/RB7: 25K.3, 27G.16, 27H.5, 27K.3
/RB8: 25K.41, 27G.14, 27H.6, 27K.41
/RB9: 25K.40, 27G.12, 27H.9, 27K.40
/RB10: 25K.39, 27G.9, 27H.12, 27K.39
/RB11: 25K.38, 27G.7, 27H.15, 27K.38
/RB12: 25K.37, 27G.5, 27H.16, 27K.37
/RB13: 25K.36, 27G.3, 27H.19, 27K.36
/RB14: 25K.35, 26G.2, 26H.2, 27K.35
/RB15: 25K.34, 26G.5, 26H.5, 27K.34
/RB16: 25K.33, 26G.6, 26H.6, 27K.33
/RB17: 25K.2, 26G.9, 26H.9, 27K.2
/RB18: 25K.1, 26G.12, 26H.12, 27K.1
/RB19: 25K.42, 26G.15, 26H.15, 27K.42
/RCLK: 16B.13, S1.1
/RES: 3F.13, I1.7, S1.10
/ROMCS: 15E.12, 23D.113
/R/~W: 3G.11, 4F.1, 5G.12, 7E.9, 10H.10, 10H.13, I1.37
/SCRCS: 23C.112, 23D.62
/SDI0: 17L.19, J3.95, J8.95
/SHD0: 17L.17, K3.48
/SHD1: 17L.18, K3.49
/SNDCLK: 1E.6, 2D.24, 11C.5
/SNDOKI0: 1E.14, 2D.10, 2E.11, 3E.11, 5D.2, 5E.11, U6.37
/SNDOKI1: 1E.15, 2D.12, 2E.12, 3E.12, 5D.5, 5E.12, U6.38
/SNDOKI2: 1E.12, 2D.13, 2E.13, 3E.13, 5D.6, 5E.13, U6.39
/SNDOKI3: 1E.8, 2D.14, 2E.15, 3E.15, 5D.9, 5E.15, U6.40
/SNDOKI4: 1E.7, 2D.15, 2E.16, 3E.16, 5D.12, 5E.16, U6.41
/SNDOKI5: 1E.9, 2D.16, 2E.17, 3E.17, 5D.15, 5E.17, U6.42
/SNDOKI6: 1E.10, 2D.17, 2E.18, 3E.18, 5D.16, 5E.18, U6.43
/SNDOKI7: 1E.13, 2D.18, 2E.19, 3E.19, 5D.19, 5E.19, U6.44
/SNS_A0: 1E.30, 2D.4, 2E.10, 3E.10, 5E.10
/SVA0: 11B.10, 12B.10, 15B1.4
/SVA1: 11B.9, 12B.9, 15B1.7
/SVA2: 11B.8, 12B.8, 15B1.9
/SVA3: 11B.7, 12B.7, 15B1.12
/SVA4: 11B.6, 12B.6, 22B.4
/SVA5: 11B.5, 12B.5, 22B.7
/SVA6: 11B.4, 12B.4, 22B.9
/SVA7: 11B.3, 12B.3, 22B.12
/SVA8: 11B.25, 12B.25, 16C.4
/SVA9: 11B.24, 12B.24, 16C.7
/SVA10: 11B.21, 12B.21, 16C.9
/SVA11: 11B.23, 12B.23, 16C.12
/SVA12: 11B.2, 12B.2, 14C.4
/S~OE: 11B.22, 12B.22, 14C.7
/TMG2TD2: 23B.4, 23C.95, 23D.124, 25B.1
/WR_SEL: 6J.9, 6J.12, 10H.8, 13H.10, 13H.12, 14C.14, 24G.13
/analog/R10: 1B.1, 1B.2
/colmix/OCOL0: 15D.2, J8.34
/colmix/OCOL1: 15D.5, J8.35
/colmix/OCOL2: 15D.6, J8.36
/colmix/OCOL3: 15D.9, J8.37
/colmix/OCOL4: 15D.12, J3.37
/colmix/OCOL5: 15D.15, J3.38
/colmix/OCOLR0: 18E.4, J3.30, J8.30
/colmix/OCOLR1: 18E.7, J3.31, J8.31
/colmix/OCOLR2: 18E.9, J3.32, J8.32
/colmix/OCOLR3: 18E.12, J3.33, J8.33
/colmix/PR01: 17L.6, J3.98
/colmix/PR02: 17L.9, J3.99
/colmix/PR03: 17L.12, J3.100
/colmix/PR04: 17L.15, J3.1
/colmix/PR05: 17L.16, J3.2
/colmix/rgb/B0: 13A.13, 13B.2
/colmix/rgb/B1: 10A.13, 13B.5
/colmix/rgb/B2: 13A.1, 13B.6
/colmix/rgb/B3: 13A.3, 13B.9
/colmix/rgb/B4: 12A.3, 13B.12
/colmix/rgb/G0: 11A.9, 14B.6
/colmix/rgb/G1: 12A.11, 14B.9
/colmix/rgb/G2: 11A.11, 14B.12
/colmix/rgb/G3: 10A.5, 14B.15
/colmix/rgb/G4: 13A.5, 14B.16
/colmix/rgb/R0: 13A.9, 13B.15
/colmix/rgb/R1: 12A.5, 13B.16
/colmix/rgb/R2: 13A.11, 13B.19
/colmix/rgb/R3: 12A.9, 14B.2
/colmix/rgb/R4: 10A.3, 14B.5
/colmix/rgb/RGB0: 10B.18, 11B.11, 13B.3
/colmix/rgb/RGB1: 10B.17, 11B.12, 13B.4
/colmix/rgb/RGB2: 10B.16, 11B.13, 13B.7
/colmix/rgb/RGB3: 10B.15, 11B.15, 13B.8
/colmix/rgb/RGB4: 10B.14, 11B.16, 13B.13
/colmix/rgb/RGB5: 10B.13, 11B.17, 13B.14
/colmix/rgb/RGB6: 10B.12, 11B.18, 13B.17
/colmix/rgb/RGB7: 10B.11, 11B.19, 13B.18
/colmix/rgb/RGB8: 12B.11, 14B.3, 14E.18
/colmix/rgb/RGB9: 12B.12, 14B.4, 14E.17
/colmix/rgb/RGB10: 12B.13, 14B.7, 14E.16
/colmix/rgb/RGB11: 12B.15, 14B.8, 14E.15
/colmix/rgb/RGB12: 12B.16, 14B.13, 14E.14
/colmix/rgb/RGB13: 12B.17, 14B.14, 14E.13
/colmix/rgb/RGB14: 12B.18, 14B.17, 14E.12
/colmix/rgb/SHAD: 12B.19, 14B.18, 14E.11
/main/CRES: 3G.9, I1.12
/main/DTACK: 7E.10, 18G.14
/main/~CCO: 16B.9, I1.36
/objects/CLKOBJ': 4J.11, 4K.11, 4L.11, 4M.11, 5J.11, 5K.11, 5L.11, 5M.11, K4.66
/objects/EA1: 6K.10, 7K.10, 11K.18, K4.112
/objects/EA2: 6K.9, 7K.9, 11K.17, K4.110
/objects/EA3: 6K.8, 7K.8, 11K.16, K4.109
/objects/EA4: 6K.7, 7K.7, 11K.15, K4.108
/objects/EA5: 6K.6, 7K.6, 11K.14, K4.107
/objects/EN0: 6K.5, 7K.5, 11K.13, K4.105
/objects/EN1: 6K.4, 7K.4, 11K.12, K4.104
/objects/EN2: 6K.3, 7K.3, 11K.11, K4.103
/objects/EN3: 6K.25, 7K.25, 8K.18, K4.102
/objects/EN4: 6K.24, 7K.24, 8K.17, K4.100
/objects/EN5: 6K.21, 7K.21, 8K.16, K4.99
/objects/EN6: 6K.23, 7K.23, 8K.15, K4.98
/objects/EN7: 6K.2, 7K.2, 8K.14, K4.97
/objects/G2D0: K3.119, K4.32
/objects/G2D1: K3.118, K4.33
/objects/G2D2: K3.117, K4.34
/objects/G2D3: K3.116, K4.35
/objects/G2D4: K3.115, K4.36
/objects/G2D5: K3.114, K4.37
/objects/G2D6: K3.113, K4.38
/objects/G2D7: K3.112, K4.39
/objects/G2D8: K3.110, K4.40
/objects/G2D9: K3.109, K4.42
/objects/G2D10: K3.108, K4.43
/objects/G2D11: K3.107, K4.44
/objects/G2D12: K3.105, K4.45
/objects/G2D13: K3.104, K4.47
/objects/G2D14: K3.103, K4.48
/objects/G2D15: K3.102, K4.49
/objects/G2D16: K3.100, K4.50
/objects/G2D17: K3.99, K4.52
/objects/G2D18: K3.98, K4.53
/objects/G2D19: K3.97, K4.54
/objects/G2D20: K3.96, K4.55
/objects/G2D21: K3.95, K4.56
/objects/LUTD0: 6K.11, 9K.18, K4.30
/objects/LUTD1: 6K.12, 9K.17, K4.29
/objects/LUTD2: 6K.13, 9K.16, K4.28
/objects/LUTD3: 6K.15, 9K.15, K4.27
/objects/LUTD4: 6K.16, 9K.14, K4.26
/objects/LUTD5: 6K.17, 9K.13, K4.25
/objects/LUTD6: 6K.18, 9K.12, K4.24
/objects/LUTD7: 6K.19, 9K.11, K4.23
/objects/LUTD8: 7K.11, 10K.18, K4.22
/objects/LUTD9: 7K.12, 10K.17, K4.20
/objects/LUTD10: 7K.13, 10K.16, K4.19
/objects/LUTD11: 7K.15, 10K.15, K4.18
/objects/LUTD12: 7K.16, 10K.14, K4.17
/objects/LUTD13: 7K.17, 10K.13, K4.15
/objects/LUTD14: 7K.18, 10K.12, K4.14
/objects/LUTD15: 7K.19, 10K.11, K4.13
/objects/M12: 3H.8, K3.10, K4.10
/objects/OBJROMA0: 1L.10, 3J.10, 3L.10, H1.10, K4.68
/objects/OBJROMA1: 1L.9, 3J.9, 3L.9, H1.9, K4.69
/objects/OBJROMA2: 1L.8, 3J.8, 3L.8, H1.8, K4.70
/objects/OBJROMA3: 1L.7, 3J.7, 3L.7, H1.7, K4.72
/objects/OBJROMA4: 1L.6, 3J.6, 3L.6, H1.6, K4.73
/objects/OBJROMA5: 1L.5, 3J.5, 3L.5, H1.5, K4.74
/objects/OBJROMA6: 1L.4, 3J.4, 3L.4, H1.4, K4.75
/objects/OBJROMA7: 1L.3, 3J.3, 3L.3, H1.3, K4.77
/objects/OBJROMA8: 1L.41, 3J.41, 3L.41, H1.41, K4.78
/objects/OBJROMA9: 1L.40, 3J.40, 3L.40, H1.40, K4.79
/objects/OBJROMA10: 1L.39, 3J.39, 3L.39, H1.39, K4.80
/objects/OBJROMA11: 1L.38, 3J.38, 3L.38, H1.38, K4.82
/objects/OBJROMA12: 1L.37, 3J.37, 3L.37, H1.37, K4.83
/objects/OBJROMA13: 1L.36, 3J.36, 3L.36, H1.36, K4.84
/objects/OBJROMA14: 1L.35, 3J.35, 3L.35, H1.35, K4.85
/objects/OBJROMA15: 1L.34, 3J.34, 3L.34, H1.34, K4.86
/objects/OBJROMA16: 1L.33, 3J.33, 3L.33, H1.33, K4.87
/objects/OBJROMA17: 1L.2, 3J.2, 3L.2, H1.2, K4.88
/objects/OBJROMA18: 1L.1, 3J.1, 3L.1, H1.1, K4.89
/objects/OBJROMA19: 1L.42, 3J.42, 3L.42, H1.42, K4.90
/objects/OBJROMD'0: 4J.2, 5J.2, 5L.2, 5M.2, K3.72
/objects/OBJROMD'1: 4J.5, 5J.5, 5L.5, 5M.5, K3.73
/objects/OBJROMD'2: 4J.6, 5J.6, 5L.6, 5M.6, K3.74
/objects/OBJROMD'3: 4J.9, 5J.9, 5L.9, 5M.9, K3.75
/objects/OBJROMD'4: 4J.12, 5J.12, 5L.12, 5M.12, K3.77
/objects/OBJROMD'5: 4J.15, 5J.15, 5L.15, 5M.15, K3.78
/objects/OBJROMD'6: 4J.16, 5J.16, 5L.16, 5M.16, K3.79
/objects/OBJROMD'7: 4J.19, 5J.19, 5L.19, 5M.19, K3.80
/objects/OBJROMD'8: 4K.2, 4L.2, 4M.2, 5K.2, K3.82
/objects/OBJROMD'9: 4K.5, 4L.5, 4M.5, 5K.5, K3.83
/objects/OBJROMD'10: 4K.6, 4L.6, 4M.6, 5K.6, K3.84
/objects/OBJROMD'11: 4K.9, 4L.9, 4M.9, 5K.9, K3.85
/objects/OBJROMD'12: 4K.12, 4L.12, 4M.12, 5K.12, K3.86
/objects/OBJROMD'13: 4K.15, 4L.15, 4M.15, 5K.15, K3.87
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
